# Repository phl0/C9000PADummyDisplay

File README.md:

# C9000PADummyDisplay
Small PCB to carry C9000PADummy with 7-segment LED 

This is a small carrier PCB to mount an Arduino Nano with a 7-segemnt LED to show the configured power level of the Ericsson C9000PADummy. For software and wiring please see: https://github.com/rwth-afu/C9000PADummy.

## Revisions

### Revision 0.1
Initial draft. Working fine so far.

## BOM

You will need a 7-segement LED module and 8 resistors 270Ohm in 0805 size. There is a [Reichelt shopping cart](https://www.reichelt.de/my/1502942).

## License
This project is released under the Creative Commons Attribution-NonCommercial-ShareAlike 3.0 (CC-BY-NC-SA 3.0, https://creativecommons.org/licenses/by-nc-sa/3.0/) license. You may edit and share it as you like, as long as credit is given and the license is not changed. You can build as many boards for you and your friends as you like and you can even sell it to them to cover your costs, **however it is strictly forbidden to turn this into a commercial product! You are not allowed to build and sell these boards for profit!**

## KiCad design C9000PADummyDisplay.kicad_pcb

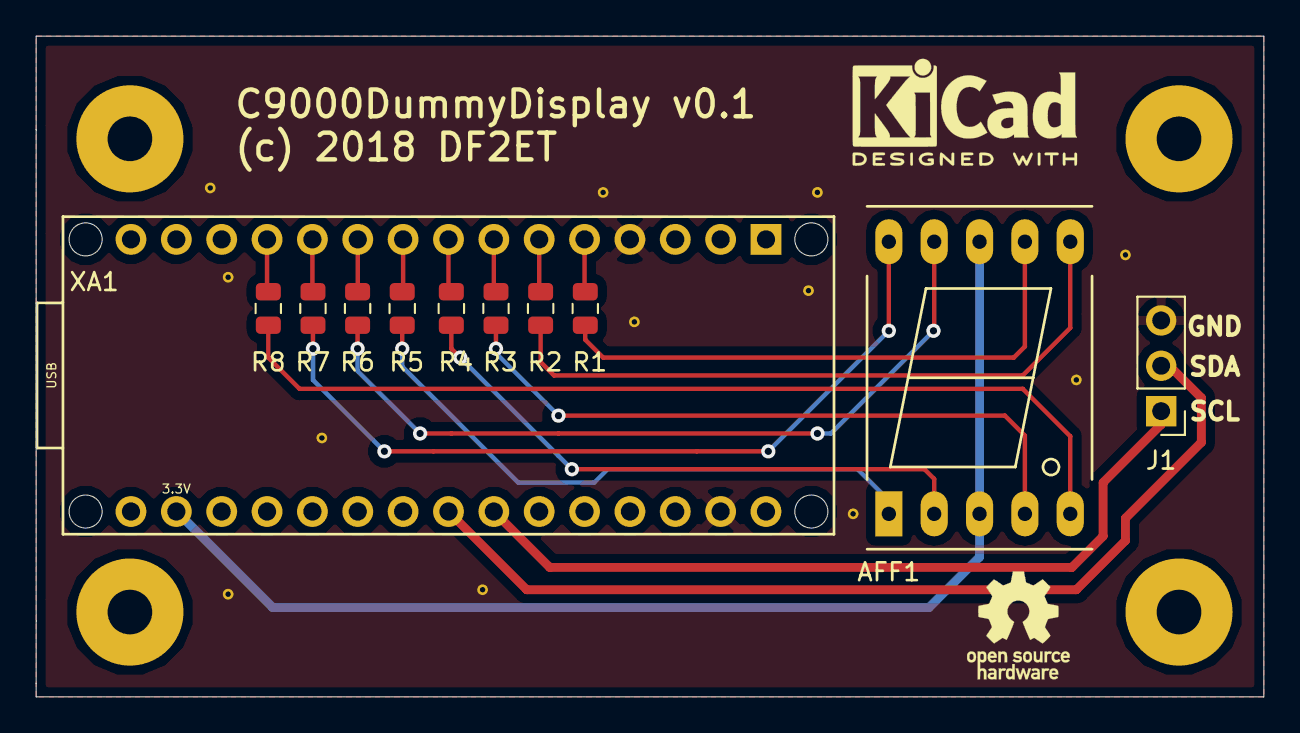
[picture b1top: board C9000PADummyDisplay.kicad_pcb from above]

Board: 2 copper layers, 68.8 x 37.0 mm, 11 parts (0 on the bottom side), 20 nets.

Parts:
AFF1: LTS-6960HR; 7SegmentLED_LTS6760_LTS6780
J1: Conn_01x03; PinHeader_1x03_P2.54mm_Vertical
R1, R2, R3, R4, R5, R6, R7, R8: 270; R_0805_2012Metric
XA1: Arduino_Nano_Socket

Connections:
+3V3: AFF1.3, AFF1.8, XA1.3V3
A: R1.2, XA1.D2
B: R2.2, XA1.D3
C: R3.2, XA1.D4
D: R4.2, XA1.D5
DP: R8.2, XA1.D9
E: R5.2, XA1.D6
F: R6.2, XA1.D7
G: R7.2, XA1.D8
GND: J1.3, XA1.GND1, XA1.GND2
unnamed: AFF1.1, R5.1
unnamed: AFF1.2, R4.1
unnamed: AFF1.4, R3.1
unnamed: AFF1.5, R8.1
unnamed: AFF1.6, R2.1
unnamed: AFF1.7, R1.1
unnamed: AFF1.9, R6.1
unnamed: AFF1.10, R7.1
SCL: J1.1, XA1.A5
SDA: J1.2, XA1.A4

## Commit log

2018-09-06 Add README and a nice picture

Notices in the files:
C9000PADummyDisplay.kicad_pcb:
(c) 2018 DF2ET
